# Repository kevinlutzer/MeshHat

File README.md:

# MeshHat

> A standard Raspberry Pi HAT with everything needed to run [MeshCore](https://meshcore.io) or [Meshtastic](https://meshtastic.org) — right out of the box.

---

## Overview

MeshHat is a Raspberry Pi HAT (Hardware Attached on Top) that integrates all the components required to join or extend a LoRa mesh network. Whether you're building an internet gateway, running automations, or deploying a remote node, MeshHat gives you a single-board solution with no additional wiring.

---

## Features

| Component | Details |
|---|---|
| **LoRa Module** | E22P — 1W output power |
| **Radio Driver MCU** | RP2040 |
| **Programming Interface** | SWD connector (for RP2040 firmware updates) |
| **Host Interface** | UART0 (Raspberry Pi ↔ RP2040) |
| **Remote Flashing** | SWD lines routed to Raspberry Pi GPIO |

---

## How It Works

Communication between the RP2040 (which handles radio duties) and the Raspberry Pi host runs over **UART0**. The RP2040 can also be **reflashed remotely** via the SWD lines connected to the Pi — no physical access to the board required for firmware updates.

---

## Example Applications

- **Internet Gateway** — Bridge a LoRa mesh network to the internet
- **Mesh Automations** — Trigger actions based on mesh messages or node events
- **Remote Sensor Node** — Deploy a standalone, Pi-powered mesh node

---

## Compatible Firmware

- [MeshCore](https://meshcore.io)
- [Meshtastic](https://meshtastic.org)

---

## Getting Started

> ⚠️ *Documentation in progress. Pinout diagrams, setup guides, and firmware flashing instructions coming soon.*

---

## Contributing

Pull requests and issue reports are welcome. If you've built something with MeshHat, we'd love to hear about it.

---

## License

*To be specified.*

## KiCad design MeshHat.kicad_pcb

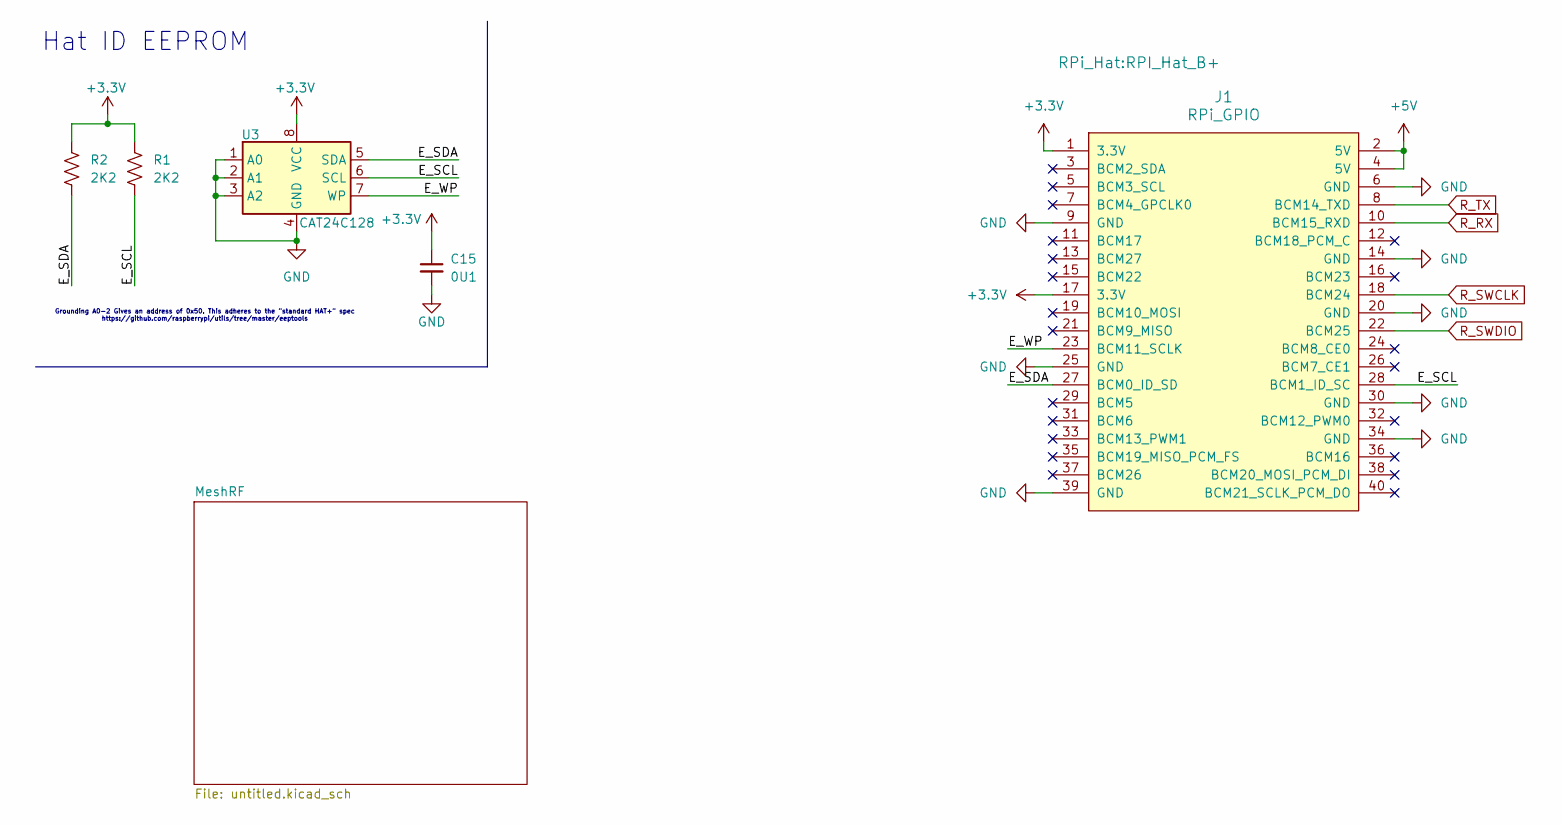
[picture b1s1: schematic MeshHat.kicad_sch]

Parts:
C15: 0U1; C_0603_1608Metric
J1: RPi_GPIO; RPI_Hat_B+
R1, R2: 2K2; R_0603_1608Metric
U3: CAT24C128; TSSOP-8_4.4x3mm_P0.65mm

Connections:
+3.3V: C15.1, J1.1 (3.3V), J1.17 (3.3V), R1.1, R2.1, U3.8 (VCC); also elsewhere on the board
+5V: J1.2 (5V), J1.4 (5V); also elsewhere on the board
/E_SCL: J1.28 (BCM1_ID_SC), R1.2, U3.6 (SCL)
/E_SDA: J1.27 (BCM0_ID_SD), R2.2, U3.5 (SDA)
/E_WP: J1.23 (BCM11_SCLK), U3.7 (WP)
GND: C15.2, J1.6 (GND), J1.9 (GND), J1.14 (GND), J1.20 (GND), J1.25 (GND), J1.30 (GND), J1.34 (GND), J1.39 (GND), U3.1 (A0), U3.2 (A1), U3.3 (A2), U3.4 (GND); also elsewhere on the board
R_RX: J1.10 (BCM15_RXD); also elsewhere on the board
R_SWCLK: J1.18 (BCM24); also elsewhere on the board
R_SWDIO: J1.22 (BCM25); also elsewhere on the board
R_TX: J1.8 (BCM14_TXD); also elsewhere on the board

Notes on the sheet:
Hat ID EEPROM
Grounding A0-2 Gives an address of 0x50. This adheres to the "standard HAT+" spec https://github.com/raspberrypi/utils/tree/master/eeptools

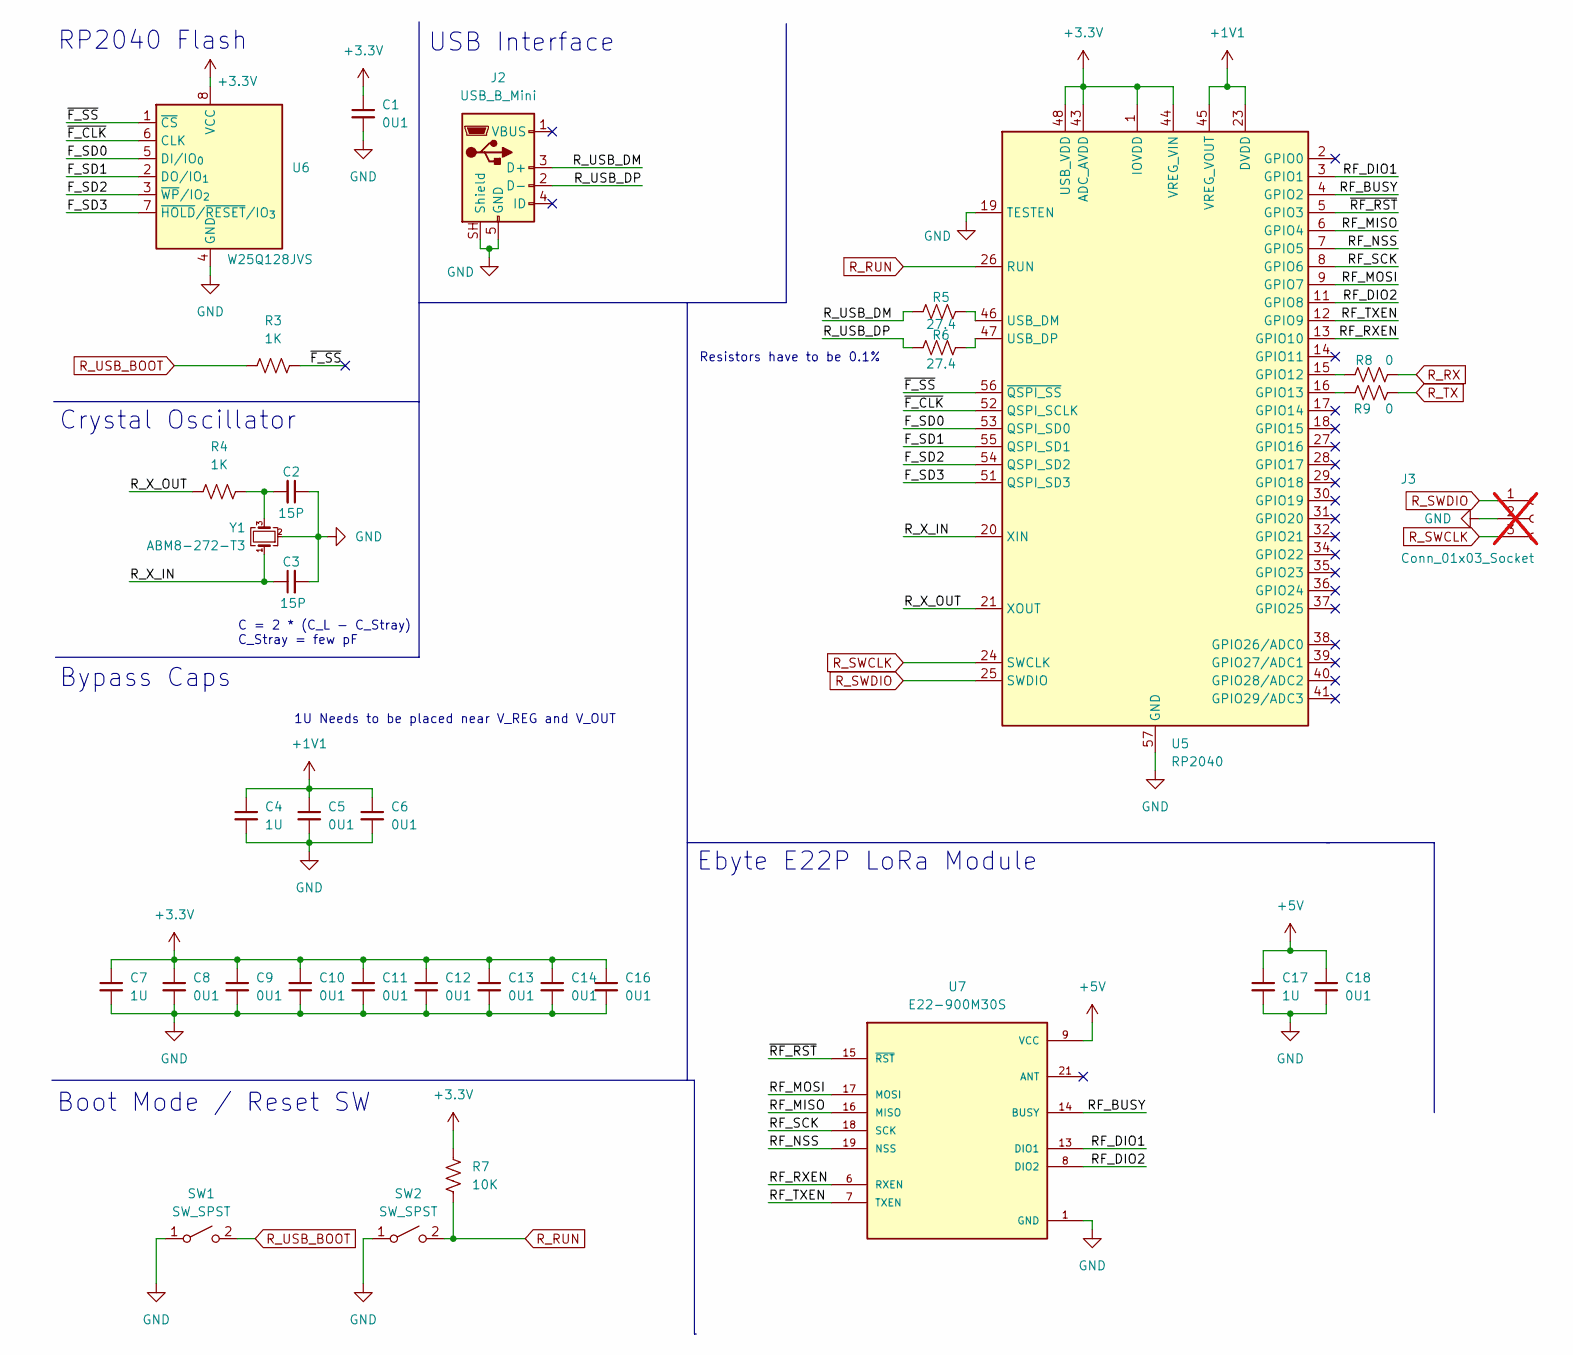
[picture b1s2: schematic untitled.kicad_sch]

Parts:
C1, C5, C6, C8, C9, C10, C11, C12, C13, C14, C16, C18: 0U1; C_0603_1608Metric
C2, C3: 15P; C_0603_1608Metric
C4, C7, C17: 1U; C_0603_1608Metric
J2: USB_B_Mini; USB_Mini-B_AdamTech_MUSB-B5-S-VT-TSMT-1_SMD_Vertical
J3: Conn_01x03_Socket; JST_SH_BM03B-SRSS-TB_1x03-1MP_P1.00mm_Vertical; not fitted
R3, R4: 1K; R_0603_1608Metric
R5, R6: 27.4; R_0603_1608Metric
R7: 10K; R_0603_1608Metric
R8, R9: 0; R_0603_1608Metric
SW1, SW2: SW_SPST; SW_Push_1P1T_NO_CK_KMR2
U5: RP2040; QFN-56-1EP_7x7mm_P0.4mm_EP3.2x3.2mm
U6: W25Q128JVS; SOIC-8_5.3x5.3mm_P1.27mm
U7: E22-900M30S; XCVR_E22-900M30S; PARTREV 1.2
Y1: ABM8-272-T3; Crystal_SMD_Abracon_ABM8G-4Pin_3.2x2.5mm

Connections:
+1V1: C4.1, C5.1, C6.1, U5.23 (DVDD), U5.45 (VREG_VOUT), U5.50 (DVDD)
+3.3V: C1.1, C7.1, C8.1, C9.1, C10.1, C11.1, C12.1, C13.1, C14.1, C16.1, R7.2, U5.1 (IOVDD), U5.10 (IOVDD), U5.22 (IOVDD), U5.33 (IOVDD), U5.42 (IOVDD), U5.43 (ADC_AVDD), U5.44 (VREG_VIN), U5.48 (USB_VDD), U5.49 (IOVDD), U6.8 (VCC); also elsewhere on the board
+5V: C17.1, C18.1, U7.9 (VCC), U7.10 (VCC); also elsewhere on the board
/MeshRF/F_SD0: U5.53 (QSPI_SD0), U6.5 (DI/IO_{0})
/MeshRF/F_SD1: U5.55 (QSPI_SD1), U6.2 (DO/IO_{1})
/MeshRF/F_SD2: U5.54 (QSPI_SD2), U6.3 (~WP/IO_{2})
/MeshRF/F_SD3: U5.51 (QSPI_SD3), U6.7 (~HOLD/~RESET/IO_{3})
/MeshRF/RF_BUSY: U5.4 (GPIO2), U7.14 (BUSY)
/MeshRF/RF_DIO1: U5.3 (GPIO1), U7.13 (DIO1)
/MeshRF/RF_DIO2: U5.11 (GPIO8), U7.8 (DIO2)
/MeshRF/RF_MISO: U5.6 (GPIO4), U7.16 (MISO)
/MeshRF/RF_MOSI: U5.9 (GPIO7), U7.17 (MOSI)
/MeshRF/RF_NSS: U5.7 (GPIO5), U7.19 (NSS)
/MeshRF/RF_RXEN: U5.13 (GPIO10), U7.6 (RXEN)
/MeshRF/RF_SCK: U5.8 (GPIO6), U7.18 (SCK)
/MeshRF/RF_TXEN: U5.12 (GPIO9), U7.7 (TXEN)
/MeshRF/R_USB_DM: J2.3 (D+), R5.1
/MeshRF/R_USB_DP: J2.2 (D-), R6.1
/MeshRF/R_X_IN: C3.1, U5.20 (XIN), Y1.1
/MeshRF/R_X_OUT: R4.1, U5.21 (XOUT)
/MeshRF/~F_CLK: U5.52 (QSPI_SCLK), U6.6 (CLK)
/MeshRF/~F_SS: R3.2, U5.56 (~QSPI_SS), U6.1 (~CS)
/MeshRF/~RF_RST: U5.5 (GPIO3), U7.15 (~RST)
GND: C1.2, C2.1, C3.2, C4.2, C5.2, C6.2, C7.2, C8.2, C9.2, C10.2, C11.2, C12.2, C13.2, C14.2, C16.2, C17.2, C18.2, J2.5 (GND), J2.SH (Shield), J3.2, SW1.1 (A), SW2.1 (A), U5.19 (TESTEN), U5.57 (GND), U6.4 (GND), U7.1 (GND), U7.2 (GND), U7.3 (GND), U7.4 (GND), U7.5 (GND), U7.11 (GND), U7.12 (GND), U7.20 (GND), U7.22 (GND), Y1.2 (G), Y1.4 (G); also elsewhere on the board
unnamed: C2.2, R4.2, Y1.3
unnamed: R8.1, U5.15 (GPIO12)
unnamed: R9.1, U5.16 (GPIO13)
unnamed: R5.2, U5.46 (USB_DM)
unnamed: R6.2, U5.47 (USB_DP)
R_RUN: R7.1, SW2.2 (B), U5.26 (RUN)
R_RX: R8.2; also elsewhere on the board
R_SWCLK: J3.3, U5.24 (SWCLK); also elsewhere on the board
R_SWDIO: J3.1, U5.25 (SWDIO); also elsewhere on the board
R_TX: R9.2; also elsewhere on the board
R_USB_BOOT: R3.1, SW1.2 (B)

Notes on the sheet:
Bypass Caps
Ebyte E22P LoRa Module
RP2040 Flash
C = 2 * (C_L - C_Stray) C_Stray = few pF
Crystal Oscillator
Resistors have to be 0.1%
Boot Mode / Reset SW
USB Interface
1U Needs to be placed near V_REG and V_OUT

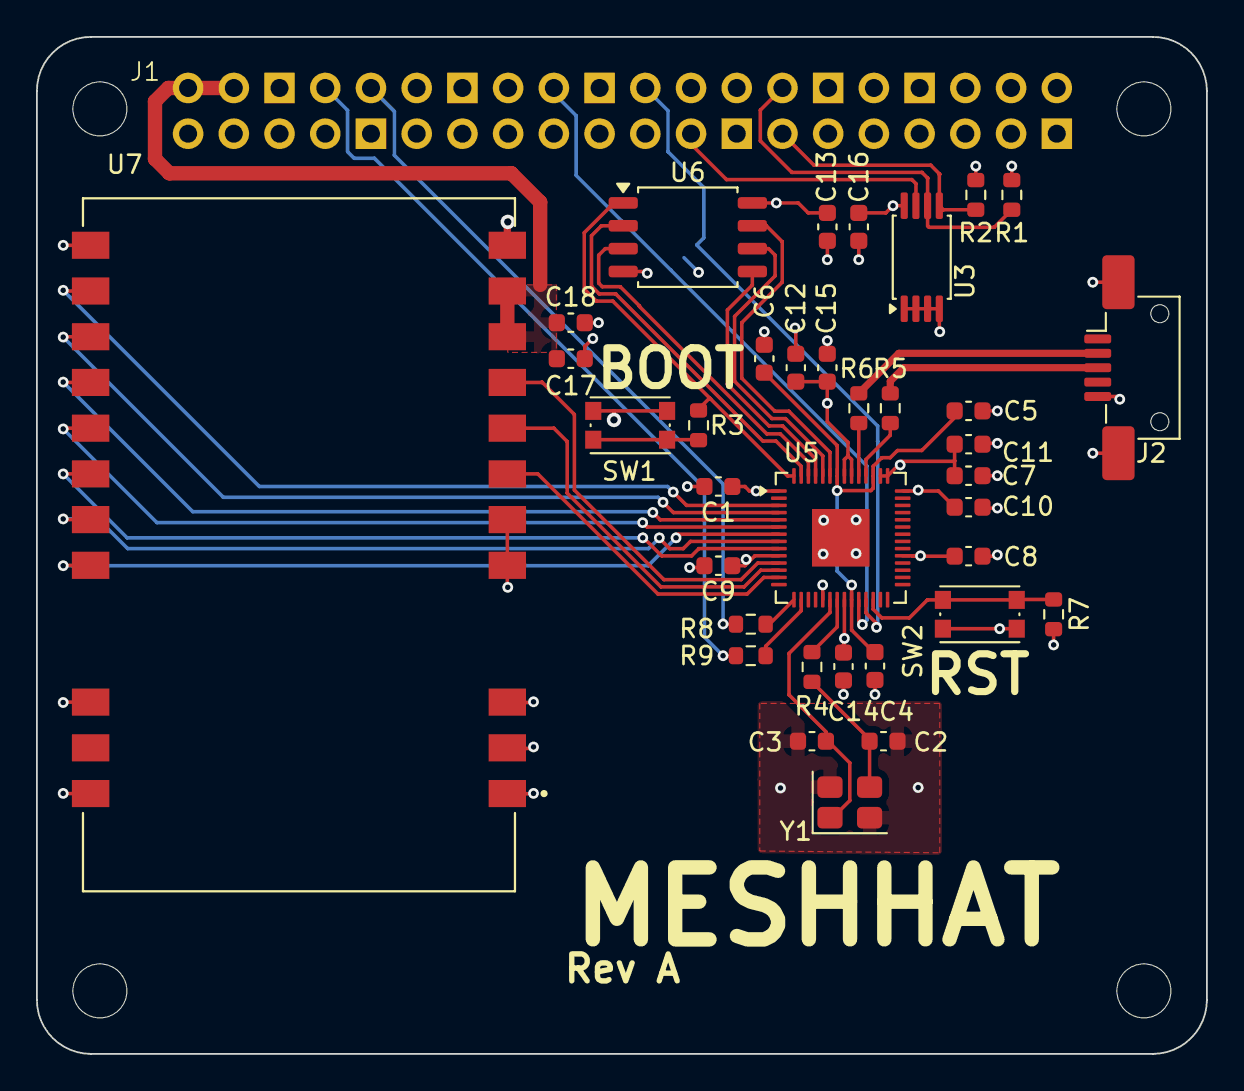
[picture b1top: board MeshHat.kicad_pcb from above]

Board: 4 copper layers, 65.0 x 56.5 mm, 37 parts (1 on the bottom side), 38 nets.

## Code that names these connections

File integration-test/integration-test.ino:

#include <RadioLib.h>
#include <SPI.h>

static constexpr uint8_t NSS = 5;  // GPIO4  – SPI0 RX
static constexpr uint8_t DIO1 = 1;  // GPIO5  – SPI0 TX
static constexpr uint8_t NRST = 3;   // GPIO6  – SPI0 SCK
static constexpr uint8_t BUSY = 2;   // GPIO7  – chip-select (active LOW)

static constexpr uint8_t RF_PIN_MISO = 4;  // GPIO4  – SPI0 RX
static constexpr uint8_t RF_PIN_MOSI = 7;  // GPIO5  – SPI0 TX
static constexpr uint8_t RF_PIN_SCK = 6;   // GPIO6  – SPI0 SCK

SX1262 radio = new Module(NSS, DIO1, NRST, BUSY);

// save transmission states between loops
int transmissionState = RADIOLIB_ERR_NONE;

// flag to indicate transmission or reception state
bool transmitFlag = false;

// flag to indicate that a packet was sent or received
volatile bool operationDone = false;

// the setup function runs once when you press reset or power the board
void setup() {
  Serial.begin(9600);
  Serial1.begin(115200);
  Serial1.setRX(pin_size_t pin);
  Serial1.setTX(pin_size_t pin);

  delay(4000);

  SPI.setMISO(RF_PIN_MISO);
  SPI.setMOSI(RF_PIN_MOSI);
  SPI.setSCK(RF_PIN_SCK);   

  // initialize digital pin LED_BUILTIN as an output.
  pinMode(LED_BUILTIN, OUTPUT);

  int state = radio.begin();
  if (state == RADIOLIB_ERR_NONE) {
    Serial.println(F("success!"));
  } else {
    Serial.print(F("failed, code "));
    Serial.println(state);
    while (true) { delay(10); }
  }

  // send the first packet on this node
  Serial.print(F("[SX1262] Sending first packet ... "));
  transmissionState = radio.startTransmit("Hello World!");
  transmitFlag = true;

  // start listening for LoRa packets on this node
  Serial.print(F("[SX1262] Starting to listen ... "));
  state = radio.startReceive();
  if (state == RADIOLIB_ERR_NONE) {
    Serial.println(F("success!"));
  } else {
    Serial.print(F("failed, code "));
    Serial.println(state);
    while (true) { delay(10); }
  }

}

// the loop function runs over and over again forever
void loop() {
  Serial.printf("What the heck %d\n", radio.randomByte());
  digitalWrite(LED_BUILTIN, LOW);  // turn the LED on (HIGH is the voltage level)
  delay(500);                      // wait for a second
  digitalWrite(LED_BUILTIN, LOW);   // turn the LED off by making the voltage LOW
  delay(500);                      // wait for a second
}

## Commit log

2026-04-10 first commit - build most of the schematic
2026-04-10 add the rest of the components and the OCD connections
2026-04-12 place all components
2026-04-12 more of the layout
2026-04-16 route more of the layout
2026-04-21 update schematic to files and add integration test
2026-04-21 more cleanup of the schematic
2026-05-03 add integration test arduino script
2026-05-04 get most of the changes in
2026-05-07 re-route the swdio lines
2026-05-17 finish off PCB, prep for review
2026-05-17 added a README
